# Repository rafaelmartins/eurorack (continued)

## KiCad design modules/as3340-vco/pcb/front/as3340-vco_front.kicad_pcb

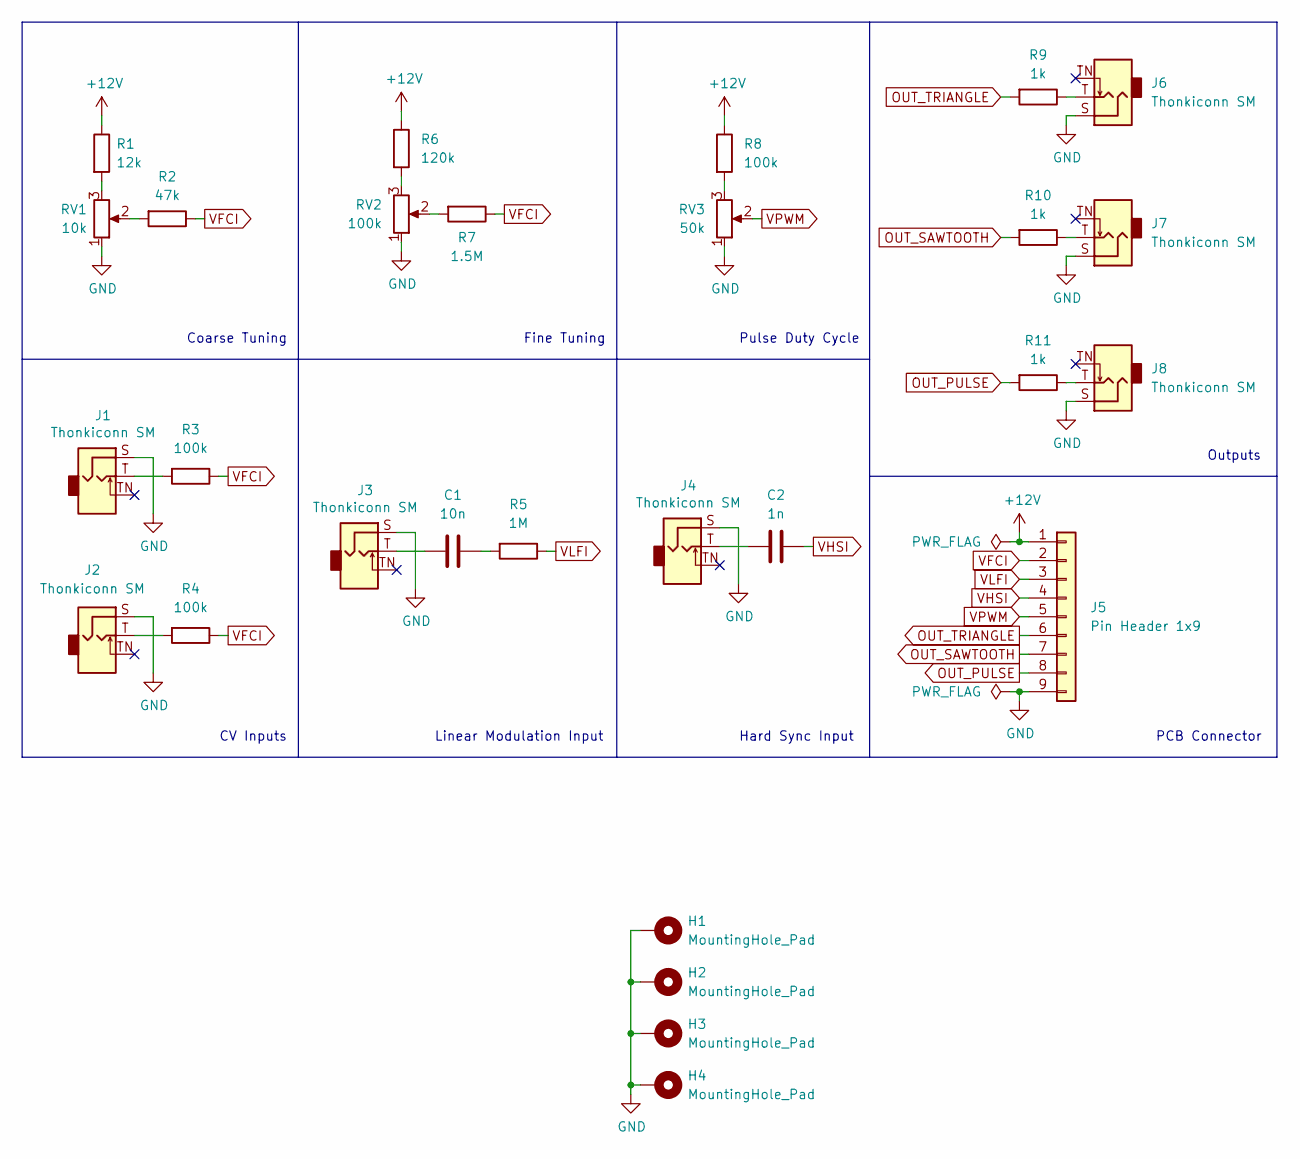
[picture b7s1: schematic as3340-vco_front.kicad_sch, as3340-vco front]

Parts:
C1: 10n; C_Disc_D3.0mm_W1.6mm_P2.50mm
C2: 1n; C_Disc_D3.0mm_W1.6mm_P2.50mm
H1, H2, H3, H4: MountingHole_Pad; MountingHole_2.2mm_M2_Pad_Via
J1, J2, J3, J4, J6, J7, J8: Thonkiconn SM; Jack_3.5mm_QingPu_WQP-PJ398SM_Vertical
J5: Pin Header 1x9; PinHeader_1x09_P2.54mm_Vertical
R1: 12k; R_Axial_DIN0207_L6.3mm_D2.5mm_P10.16mm_Horizontal
R2: 47k; R_Axial_DIN0207_L6.3mm_D2.5mm_P10.16mm_Horizontal
R3, R4, R8: 100k; R_Axial_DIN0207_L6.3mm_D2.5mm_P10.16mm_Horizontal
R5: 1M; R_Axial_DIN0207_L6.3mm_D2.5mm_P10.16mm_Horizontal
R6: 120k; R_Axial_DIN0207_L6.3mm_D2.5mm_P10.16mm_Horizontal
R7: 1.5M; R_Axial_DIN0207_L6.3mm_D2.5mm_P10.16mm_Horizontal
R9, R10, R11: 1k; R_Axial_DIN0207_L6.3mm_D2.5mm_P10.16mm_Horizontal
RV1: 10k; Potentiometer_Alpha_RD901F-40-00D_Single_Vertical_CircularH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
RV2: 100k; Potentiometer_Alpha_RD901F-40-00D_Single_Vertical_CircularH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
RV3: 50k; Potentiometer_Alpha_RD901F-40-00D_Single_Vertical_CircularH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

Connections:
+12V: J5.1, R1.1, R6.1, R8.1
GND: H1.1, H2.1, H3.1, H4.1, J1.S, J2.S, J3.S, J4.S, J5.9, J6.S, J7.S, J8.S, RV1.1, RV2.1, RV3.1
unnamed: C1.1, R5.2
unnamed: C1.2, J3.T
unnamed: C2.2, J4.T
unnamed: J1.T, R3.2
unnamed: J2.T, R4.2
unnamed: J6.T, R9.1
unnamed: J7.T, R10.1
unnamed: J8.T, R11.1
unnamed: R1.2, RV1.3
unnamed: R2.2, RV1.2
unnamed: R6.2, RV2.3
unnamed: R7.2, RV2.2
unnamed: R8.2, RV3.3
OUT_PULSE: J5.8, R11.2
OUT_SAWTOOTH: J5.7, R10.2
OUT_TRIANGLE: J5.6, R9.2
VFCI: J5.2, R2.1, R3.1, R4.1, R7.1
VHSI: C2.1, J5.4
VLFI: J5.3, R5.1
VPWM: J5.5, RV3.2

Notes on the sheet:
CV Inputs
Fine Tuning
Hard Sync Input
Outputs
Pulse Duty Cycle
PCB Connector
Linear Modulation Input
Coarse Tuning

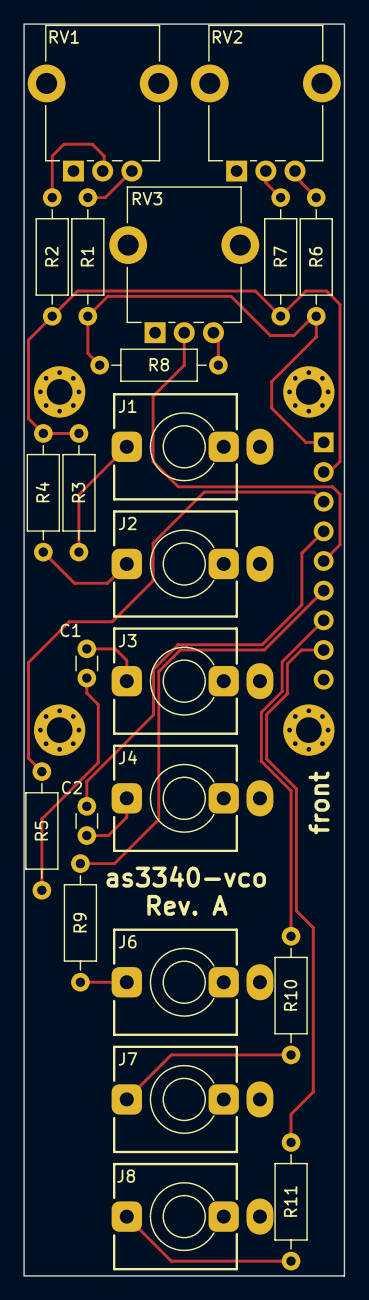
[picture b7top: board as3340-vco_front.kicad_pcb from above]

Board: 2 copper layers, 27.4 x 107.2 mm, 28 parts (1 on the bottom side), 22 nets.

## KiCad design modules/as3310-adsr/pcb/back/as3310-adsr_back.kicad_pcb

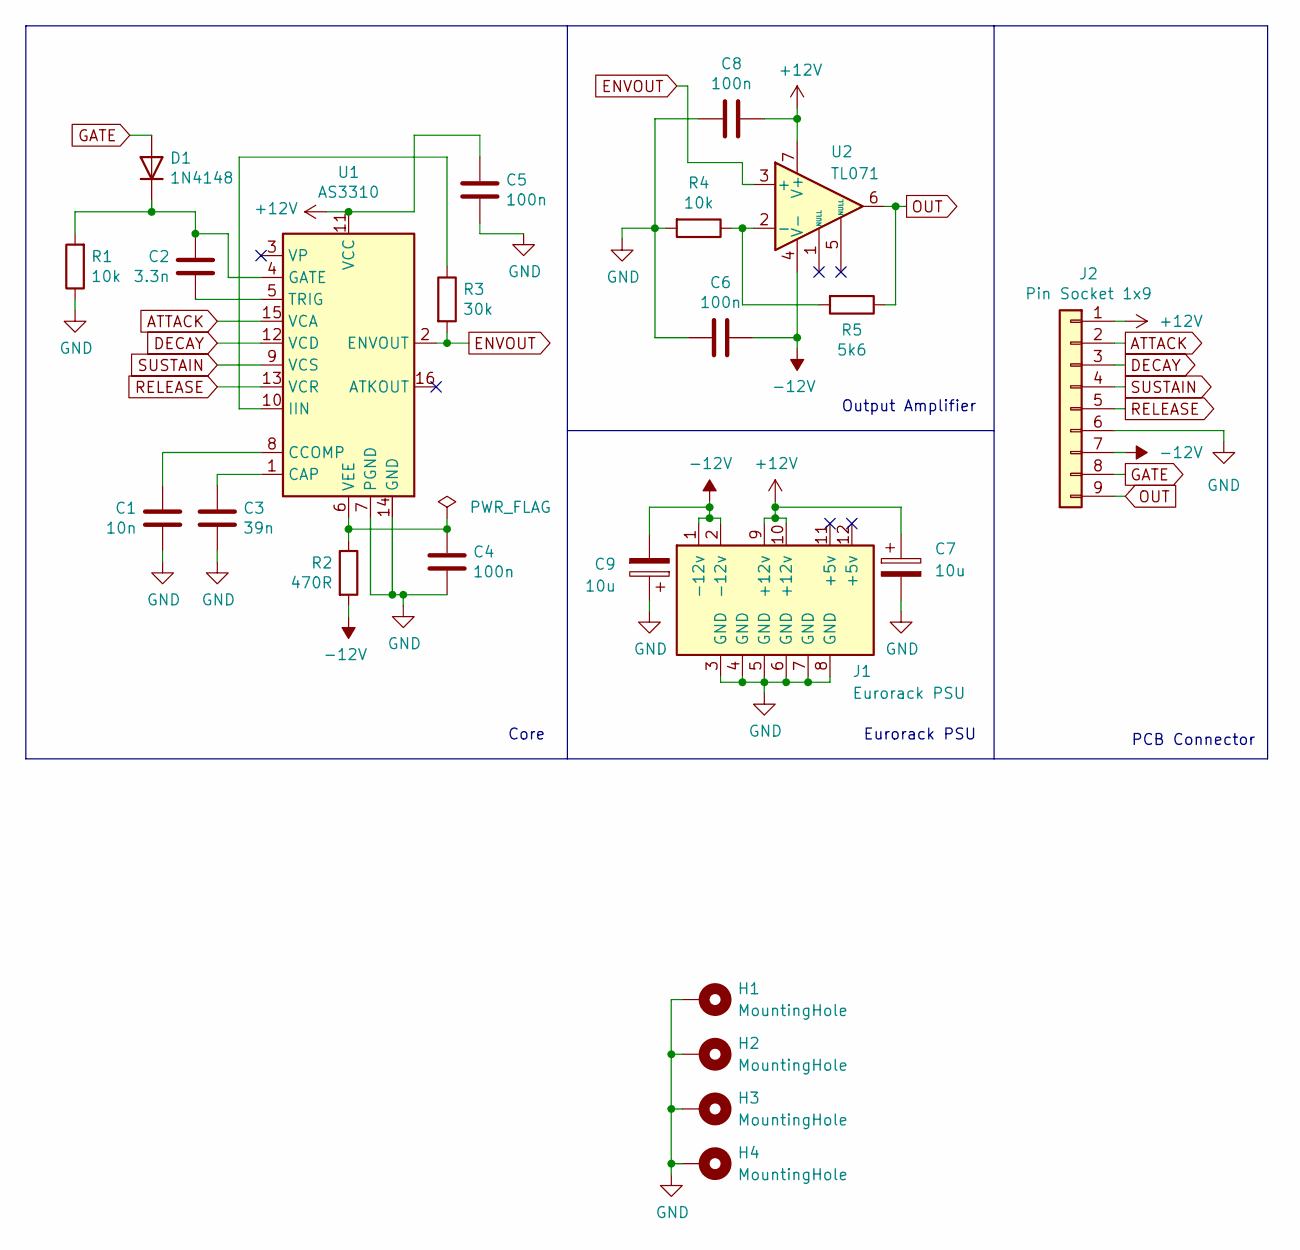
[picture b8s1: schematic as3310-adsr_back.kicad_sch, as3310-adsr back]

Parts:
C1: 10n; C_Disc_D3.0mm_W1.6mm_P2.50mm
C2: 3.3n; C_Disc_D3.0mm_W1.6mm_P2.50mm
C3: 39n; C_Rect_L13.0mm_W5.0mm_P10.00mm_FKS3_FKP3_MKS4
C4, C5, C6, C8: 100n; C_Disc_D4.3mm_W1.9mm_P5.00mm
C7, C9: 10u; CP_Radial_D5.0mm_P2.50mm
D1: 1N4148; D_DO-35_SOD27_P7.62mm_Horizontal
H1, H2, H3, H4: MountingHole; MountingHole_2.2mm_M2_Pad_Via
J1: Eurorack PSU; IDC-Header_2x08_P2.54mm_Vertical
J2: Pin Socket 1x9; PinSocket_1x09_P2.54mm_Vertical
R1, R4: 10k; R_Axial_DIN0207_L6.3mm_D2.5mm_P10.16mm_Horizontal
R2: 470R; R_Axial_DIN0207_L6.3mm_D2.5mm_P10.16mm_Horizontal
R3: 30k; R_Axial_DIN0207_L6.3mm_D2.5mm_P10.16mm_Horizontal
R5: 5k6; R_Axial_DIN0207_L6.3mm_D2.5mm_P10.16mm_Horizontal
U1: AS3310; DIP-16_W7.62mm
U2: TL071; DIP-8_W7.62mm

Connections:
+12V: C5.2, C7.1, C8.1, J1.9 (+12v), J1.10 (+12v), J2.1, U1.11 (VCC), U2.7 (V+)
-12V: C6.1, C9.2, J1.1 (-12v), J1.2 (-12v), J2.7, R2.2, U2.4 (V-)
ATTACK: J2.2, U1.15 (VCA)
DECAY: J2.3, U1.12 (VCD)
ENVOUT: R3.2, U1.2 (ENVOUT), U2.3 (+)
GATE: D1.2 (A), J2.8
GND: C1.2, C3.2, C4.1, C5.1, C6.2, C7.2, C8.2, C9.1, H1.1, H2.1, H3.1, H4.1, J1.3 (GND), J1.4 (GND), J1.5 (GND), J1.6 (GND), J1.7 (GND), J1.8 (GND), J2.6, R1.1, R4.2, U1.7 (PGND), U1.14 (GND)
unnamed: C1.1, U1.8 (CCOMP)
unnamed: C2.1, D1.1 (K), R1.2, U1.4 (GATE)
unnamed: C2.2, U1.5 (TRIG)
unnamed: C3.1, U1.1 (CAP)
unnamed: C4.2, R2.1, U1.6 (VEE)
unnamed: R3.1, U1.10 (IIN)
unnamed: R4.1, R5.2, U2.2 (-)
OUT: J2.9, R5.1, U2.6
RELEASE: J2.5, U1.13 (VCR)
SUSTAIN: J2.4, U1.9 (VCS)

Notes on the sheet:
Output Amplifier
Core
Eurorack PSU
PCB Connector

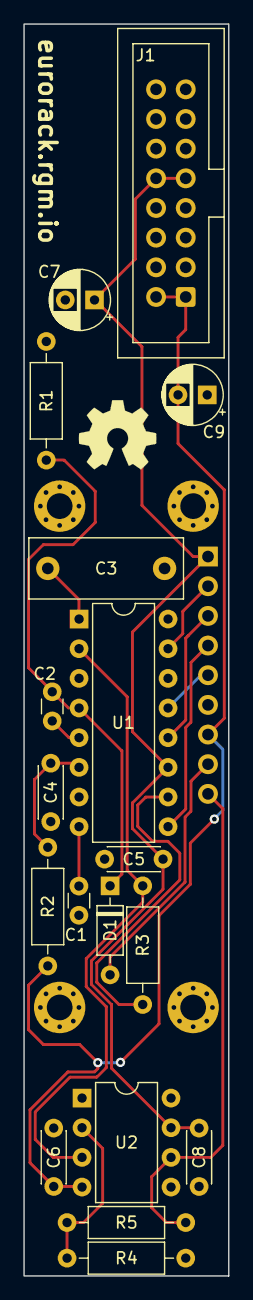
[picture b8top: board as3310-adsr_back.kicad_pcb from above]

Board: 2 copper layers, 17.5 x 107.2 mm, 23 parts (1 on the bottom side), 17 nets.

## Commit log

2022-01-03 share: openscad, kicad: initial libraries
2022-01-03 lib: usb-u2: initial import
2022-01-03 share: dwtk-makefile: initial import
2022-01-03 modules: usb-to-midi: initial version, produced and tested
2022-01-03 share: kicad: use PTH footprint for Raspberry Pi Pico
2022-01-03 modules: midi-oscillator: initial hardware version, no firmware yet
2022-01-03 modules: midi-oscilator: pcb: fix schematics and add page metadata
2022-01-03 modules: usb-to-midi, midi-oscillator: fix kicad lib description
2022-01-03 modules: as3340-vco: initial version, produced but untested. missing panel
2022-01-03 modules: midi-to-cv: initial pcb, produced but untested.
2022-01-03 share: kicad: added missing led footprint
2022-01-03 modules: midi-to-cv: fix kicad lib description
2022-01-03 usb-to-midi: fix some metadata, add schematic pdf
2022-01-04 modules: midi-oscillator: schematic improvements, added pdf
2022-01-04 modules: usb-to-midi: fix references
2022-01-04 modules: midi-to-cv: fix references
2022-01-04 modules: as3340-vco: fix references
2022-01-04 share: openscad: added led holder library
2022-01-04 modules: usb-to-midi: 3d-models: use led holder library
2022-01-04 share: openscad: added pcb holder library
2022-01-04 modules: as3340-vco: 3d-models: use pcb holder library
2022-01-04 modules: midi-oscillator: 3d-models: use pcb holder library
2022-01-04 *: added/updated SPDX headers
2022-01-04 modules: added license to schematics
2022-01-04 lib: usb-u2: update license copyright year
2022-01-04 modules: midi-to-cv: added 3d models. untested
2022-01-05 modules: as3340-vco: added panel 3d model. untested
2022-01-06 modules: as3340-vco: 3d-models: fix panel top jack position, add pot tags
2022-01-06 modules: usb-to-midi: use openmoko provided USB PID
2022-01-06 modules: usb-to-midi: firmware: recover from bad packets
2022-01-08 modules: as3310-adsr: initial version (pcbs in production), missing panel
2022-01-09 share: kicad: added a generic pad footprint
2022-01-09 prototype-pcbs: initial commit
2022-01-09 modules: as3340-vco: panel: fix potentiometer tag position
2022-01-10 modules: as3310-adsr: added a panel for my prototype
2022-01-16 modules: dso138mini: initial 3d models
2022-01-16 modules: midi-oscillator: added missing symbol library
2022-01-22 modules: as3310-adsr: new revision for back pcb: 1.1
    the module was missing a diode in the gate input to avoid burning the
    AS3310 by applying negative voltage.
    I fixed my boards by cutting and scrapping the gate track, close to R3
    top pin and soldering an SMD version of 1N4148, like this:
    https://filebin.xyz/UGnlaM44cwMN2fDaeGj87lC2
2022-01-22 modules: as3310-adsr: added panel 3d model
2022-01-23 modules: midi-splitter: initial version
2022-01-23 prototype-pcbs: added revision 2.1 for PCBs with Eurorack PSU connector.
    gerber's silkscreen was missing the voltage references in the solder
    points.
2022-01-29 modules: as3360-vca: initial version, missing panel
2022-06-27 share: kicad: upgrade libraries to kicad 6
2022-06-27 modules: midi-oscillator: back: upgrade to kicad 6
2022-06-27 modules: midi-oscillator: back: remove unconnected nets
2022-06-27 modules: midi-oscillator: front: upgrade to kicad 6
2022-06-27 modules: as3310-adsr: back: upgrade to kicad 6
2022-06-27 modules: as3310-adsr: back: remove unconnected nets
2022-06-27 modules: as3310-adsr: front: upgrade to kicad 6
2022-06-27 modules: as3310-adsr: front: remove unconnected nets
2022-06-27 modules: usb-to-midi: upgrade to kicad 6
2022-06-27 modules: usb-to-midi: remove unconnected nets
2022-06-27 modules: midi-to-cv: upgrade to kicad 6
2022-06-28 modules: as3340-vco: back: upgrade to kicad 6
2022-06-28 modules: as3340-vco: back: remove unconnected nets
2022-06-28 modules: as3340-vco: front: upgrade to kicad 6
2022-06-28 modules: as3360-vca: upgrade to kicad 6
2022-06-28 modules: as3360-vca: remove unconnected nets
2022-06-28 modules: midi-splitter: back: upgrade to kicad 6
2022-06-28 modules: midi-splitter: front: upgrade to kicad 6
2022-06-28 modules: midi-splitter: front: remove unconnected nets
2022-06-28 prototype-pcbs: 4hp: upgrade to kicad 6
2022-06-28 prototype-pcbs: 4hp-power: upgrade to kicad 6
2022-06-28 prototype-pcbs: 4hp-power: remove unconnected nets
2022-06-28 prototype-pcbs: 8hp: upgrade to kicad 6
2022-06-28 prototype-pcbs: 8hp-power: upgrade to kicad 6
2022-06-28 prototype-pcbs: 12hp: upgrade to kicad 6
2022-06-28 prototype-pcbs: 12hp-power: upgrade to kicad 6
2022-06-28 modules: prototype-pcbs: remove old cache libraries
2022-06-28 modules: as3360-vca: new revision 1.1
2022-07-08 modules: midi-oscillator: front: new revision 1.1
2022-07-08 modules: midi-oscillator: back: new revision 1.1
2022-11-20 share: kicad: added eurorack psu symbol
2022-11-20 share: kicad: fixed silkscreen violation for thonkiconn jacks
2022-11-20 share: kicad: fixed silkscreen violation for idc header boxes
2022-11-20 share: kicad: added footprints for eurorack pcb outline
2022-11-20 modules: as3310-adsr: back: revision A (redesign)
2022-11-20 modules: midi-splitter: revision A (redesign)
2022-11-20 modules: midi-to-cv: revision A (redesign)
2022-11-20 modules: as3340-vco: front: revision A (redesign)
2022-11-20 modules: as3310-adsr: front: revision A (redesign)
2022-11-20 modules: as3340-vco: back: revision A (redesign)
2022-11-20 modules: as3360-vca: revision A (redesign)
2022-11-20 modules: usb-to-midi: revision A (redesign)
